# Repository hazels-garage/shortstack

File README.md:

# shortstack

| Left | Right |
| :---: | :---: |
|   |  |

## ultrathin split ortholinear

Probably my final X Switch novelty board.  Split 6x4 ortho.  No bells or whistles.

## MATERIALS
- 48x [Kailh X Switches](https://mkultra.click/kailh-x-switches-and-keycaps/)
- 48x [1N4148 - SOD-123 Diodes](https://mkultra.click/diode-1n4148-sod-123f/)
- 2x ProMicro compatible controller
- 2x [TRRS Jack](https://mkultra.click/pj-320a-3-5mm-trrs-jack/)

## Build Details
- reversible pcb.
- solder jumpers on back of each side.
- controller is installed component side up.
- right side is connected to computer.

## FIRMWARE

[QMK](https://github.com/jasonhazel/qmk_hazel/tree/master/keyboards/jasonhazel/shortstack)

## SUPPORT

<p xmlns:cc="http://creativecommons.org/ns#" xmlns:dct="http://purl.org/dc/terms/"><a property="dct:title" rel="cc:attributionURL" href="https://github.com/jasonhazel/shortstack">shortstack</a> by <a rel="cc:attributionURL dct:creator" property="cc:attributionName" href="https://github.com/jasonhazel">Jason Hazel</a> is licensed under <a href="http://creativecommons.org/licenses/by/4.0/?ref=chooser-v1" target="_blank" rel="license noopener noreferrer" style="display:inline-block;">CC BY 4.0</a></p>

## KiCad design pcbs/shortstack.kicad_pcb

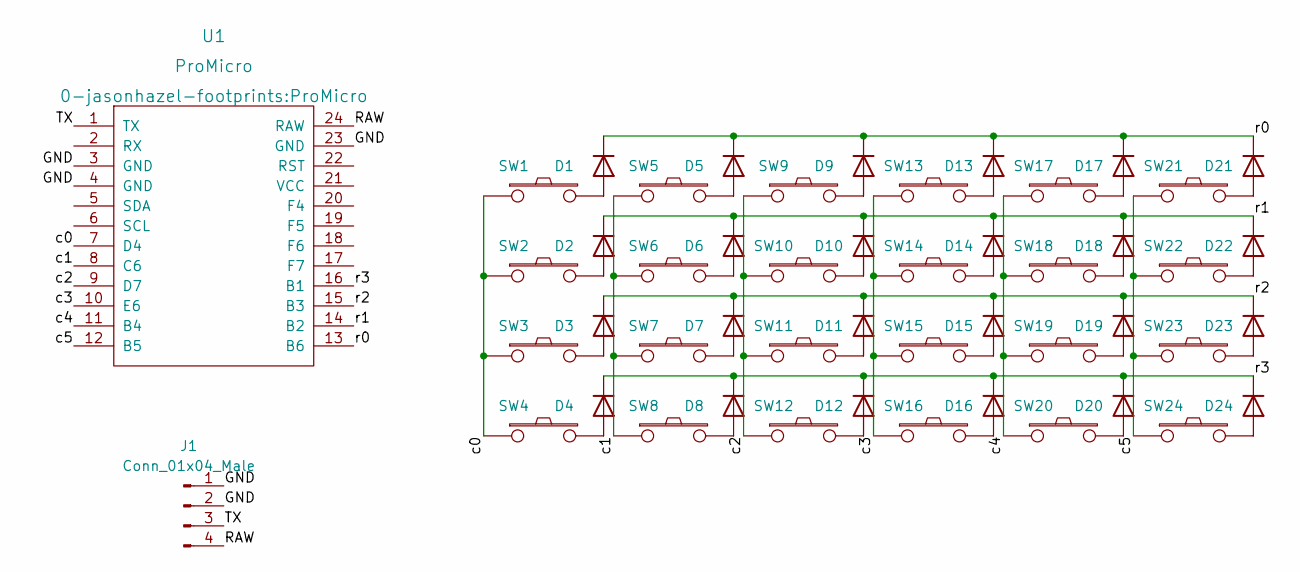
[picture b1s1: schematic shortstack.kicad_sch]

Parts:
D1, D2, D3, D4, D5, D6, D7, D8, D9, D10, D11, D12, D13, D14, D15, D16, D17, D18, D19, D20, D21, D22, D23, D24: 1N4148W; D_SOD-123-rev
J1: Conn_01x04_Male; TRRS-PJ-320A-dual
SW1, SW2, SW3, SW4, SW5, SW6, SW7, SW8, SW9, SW10, SW11, SW12, SW13, SW14, SW15, SW16, SW17, SW18, SW19, SW20, SW21, SW22, SW23, SW24: SW_PUSH; Kailh-PG1425-X-Switch-revers
U1: ProMicro

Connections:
/GND: J1.1, J1.2, U1.3 (GND), U1.4 (GND), U1.23 (GND)
/RAW: J1.4, U1.24 (RAW)
/TX: J1.3, U1.1 (TX)
/c0: SW1.1, SW2.1, SW3.1, SW4.1, U1.7 (D4)
/c1: SW5.1, SW6.1, SW7.1, SW8.1, U1.8 (C6)
/c2: SW9.1, SW10.1, SW11.1, SW12.1, U1.9 (D7)
/c3: SW13.1, SW14.1, SW15.1, SW16.1, U1.10 (E6)
/c4: SW17.1, SW18.1, SW19.1, SW20.1, U1.11 (B4)
/c5: SW21.1, SW22.1, SW23.1, SW24.1, U1.12 (B5)
/r0: D1.1 (K), D5.1 (K), D9.1 (K), D13.1 (K), D17.1 (K), D21.1 (K), U1.13 (B6)
/r1: D2.1 (K), D6.1 (K), D10.1 (K), D14.1 (K), D18.1 (K), D22.1 (K), U1.14 (B2)
/r2: D3.1 (K), D7.1 (K), D11.1 (K), D15.1 (K), D19.1 (K), D23.1 (K), U1.15 (B3)
/r3: D4.1 (K), D8.1 (K), D12.1 (K), D16.1 (K), D20.1 (K), D24.1 (K), U1.16 (B1)
unnamed: D1.2 (A), SW1.2
unnamed: D2.2 (A), SW2.2
unnamed: D3.2 (A), SW3.2
unnamed: D4.2 (A), SW4.2
unnamed: D5.2 (A), SW5.2
unnamed: D6.2 (A), SW6.2
unnamed: D7.2 (A), SW7.2
unnamed: D8.2 (A), SW8.2
unnamed: D9.2 (A), SW9.2
unnamed: D10.2 (A), SW10.2
unnamed: D11.2 (A), SW11.2
unnamed: D12.2 (A), SW12.2
unnamed: D13.2 (A), SW13.2
unnamed: D14.2 (A), SW14.2
unnamed: D15.2 (A), SW15.2
unnamed: D16.2 (A), SW16.2
unnamed: D17.2 (A), SW17.2
unnamed: D18.2 (A), SW18.2
unnamed: D19.2 (A), SW19.2
unnamed: D20.2 (A), SW20.2
unnamed: D21.2 (A), SW21.2
unnamed: D22.2 (A), SW22.2
unnamed: D23.2 (A), SW23.2
unnamed: D24.2 (A), SW24.2

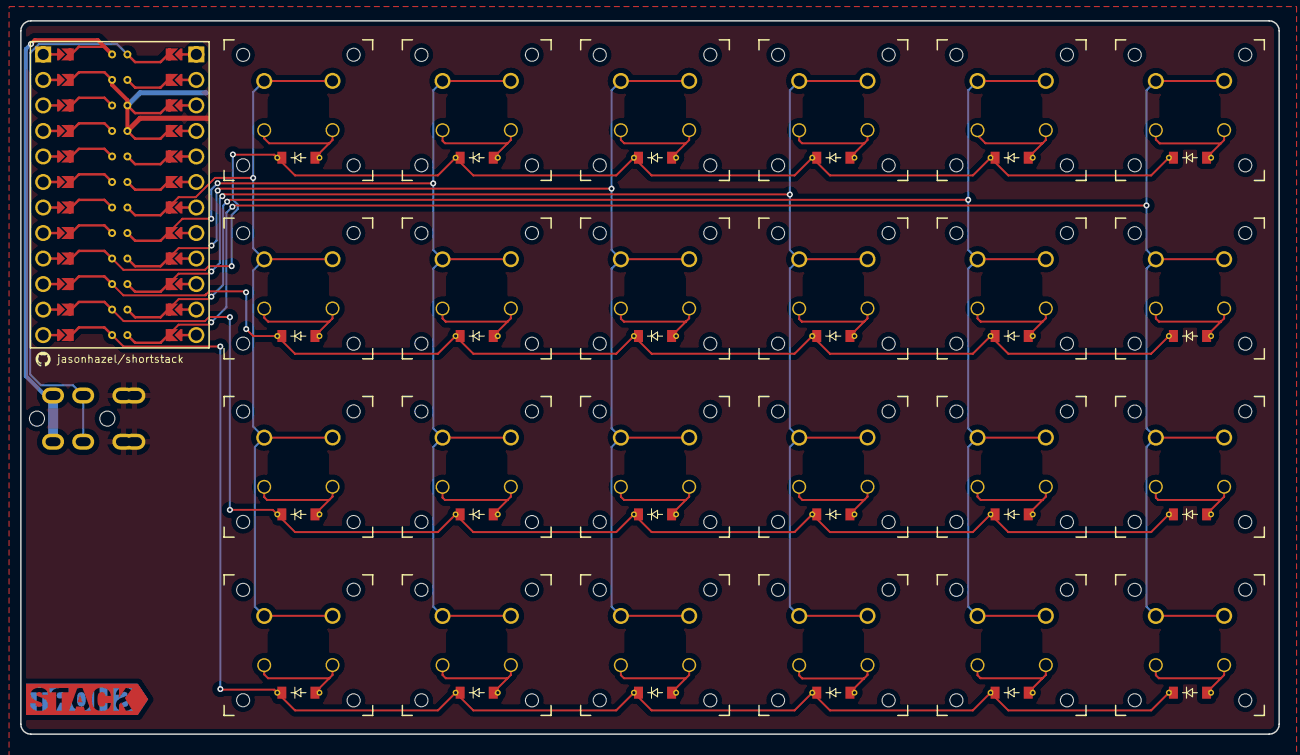
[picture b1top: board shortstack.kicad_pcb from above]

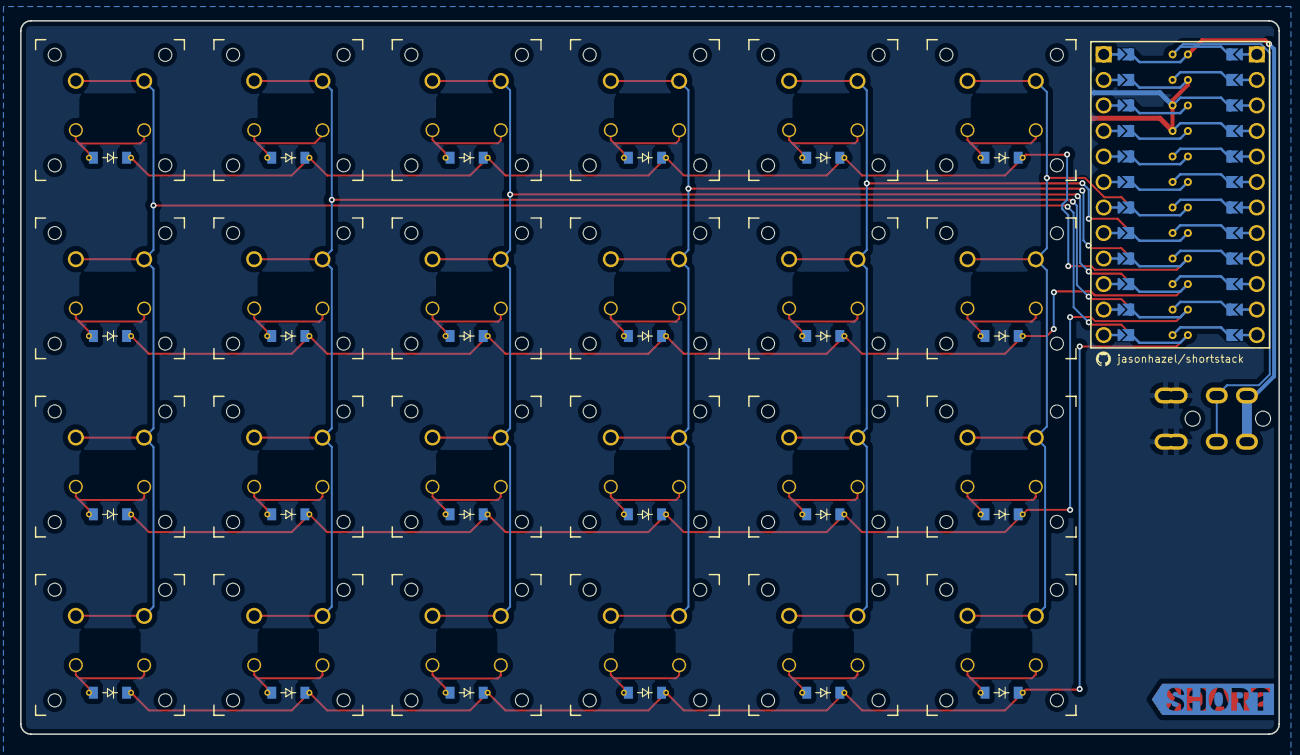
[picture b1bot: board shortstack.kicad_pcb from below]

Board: 2 copper layers, 125.2 x 71.0 mm, 54 parts (26 on the bottom side), 37 nets.

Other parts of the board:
GH2, GH2#2: jasonhazel/shortstack; github
kibuzzard-63D71E25: G***; kibuzzard-63D71E25
kibuzzard-63D71F2F: G***; kibuzzard-63D71F2F

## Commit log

2023-01-30 init
2023-01-30 fix path
2023-01-30 images dir
2023-01-30 why kibot no upload?
2023-01-30 Update gallery (automated)
2023-02-02 Update README.md
    update bom
2026-03-26 Remove Hazel's Garage badge from README
    Removed badge for Hazel's Garage from README.

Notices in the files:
README.md:
https://img.shields.io/github/license/hazels-garage/shortstack?label=%20&logo=creativecommons&logoColor=%23ffffff&style=flat-square
